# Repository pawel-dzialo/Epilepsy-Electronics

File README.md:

# Epilepsy detection electronics

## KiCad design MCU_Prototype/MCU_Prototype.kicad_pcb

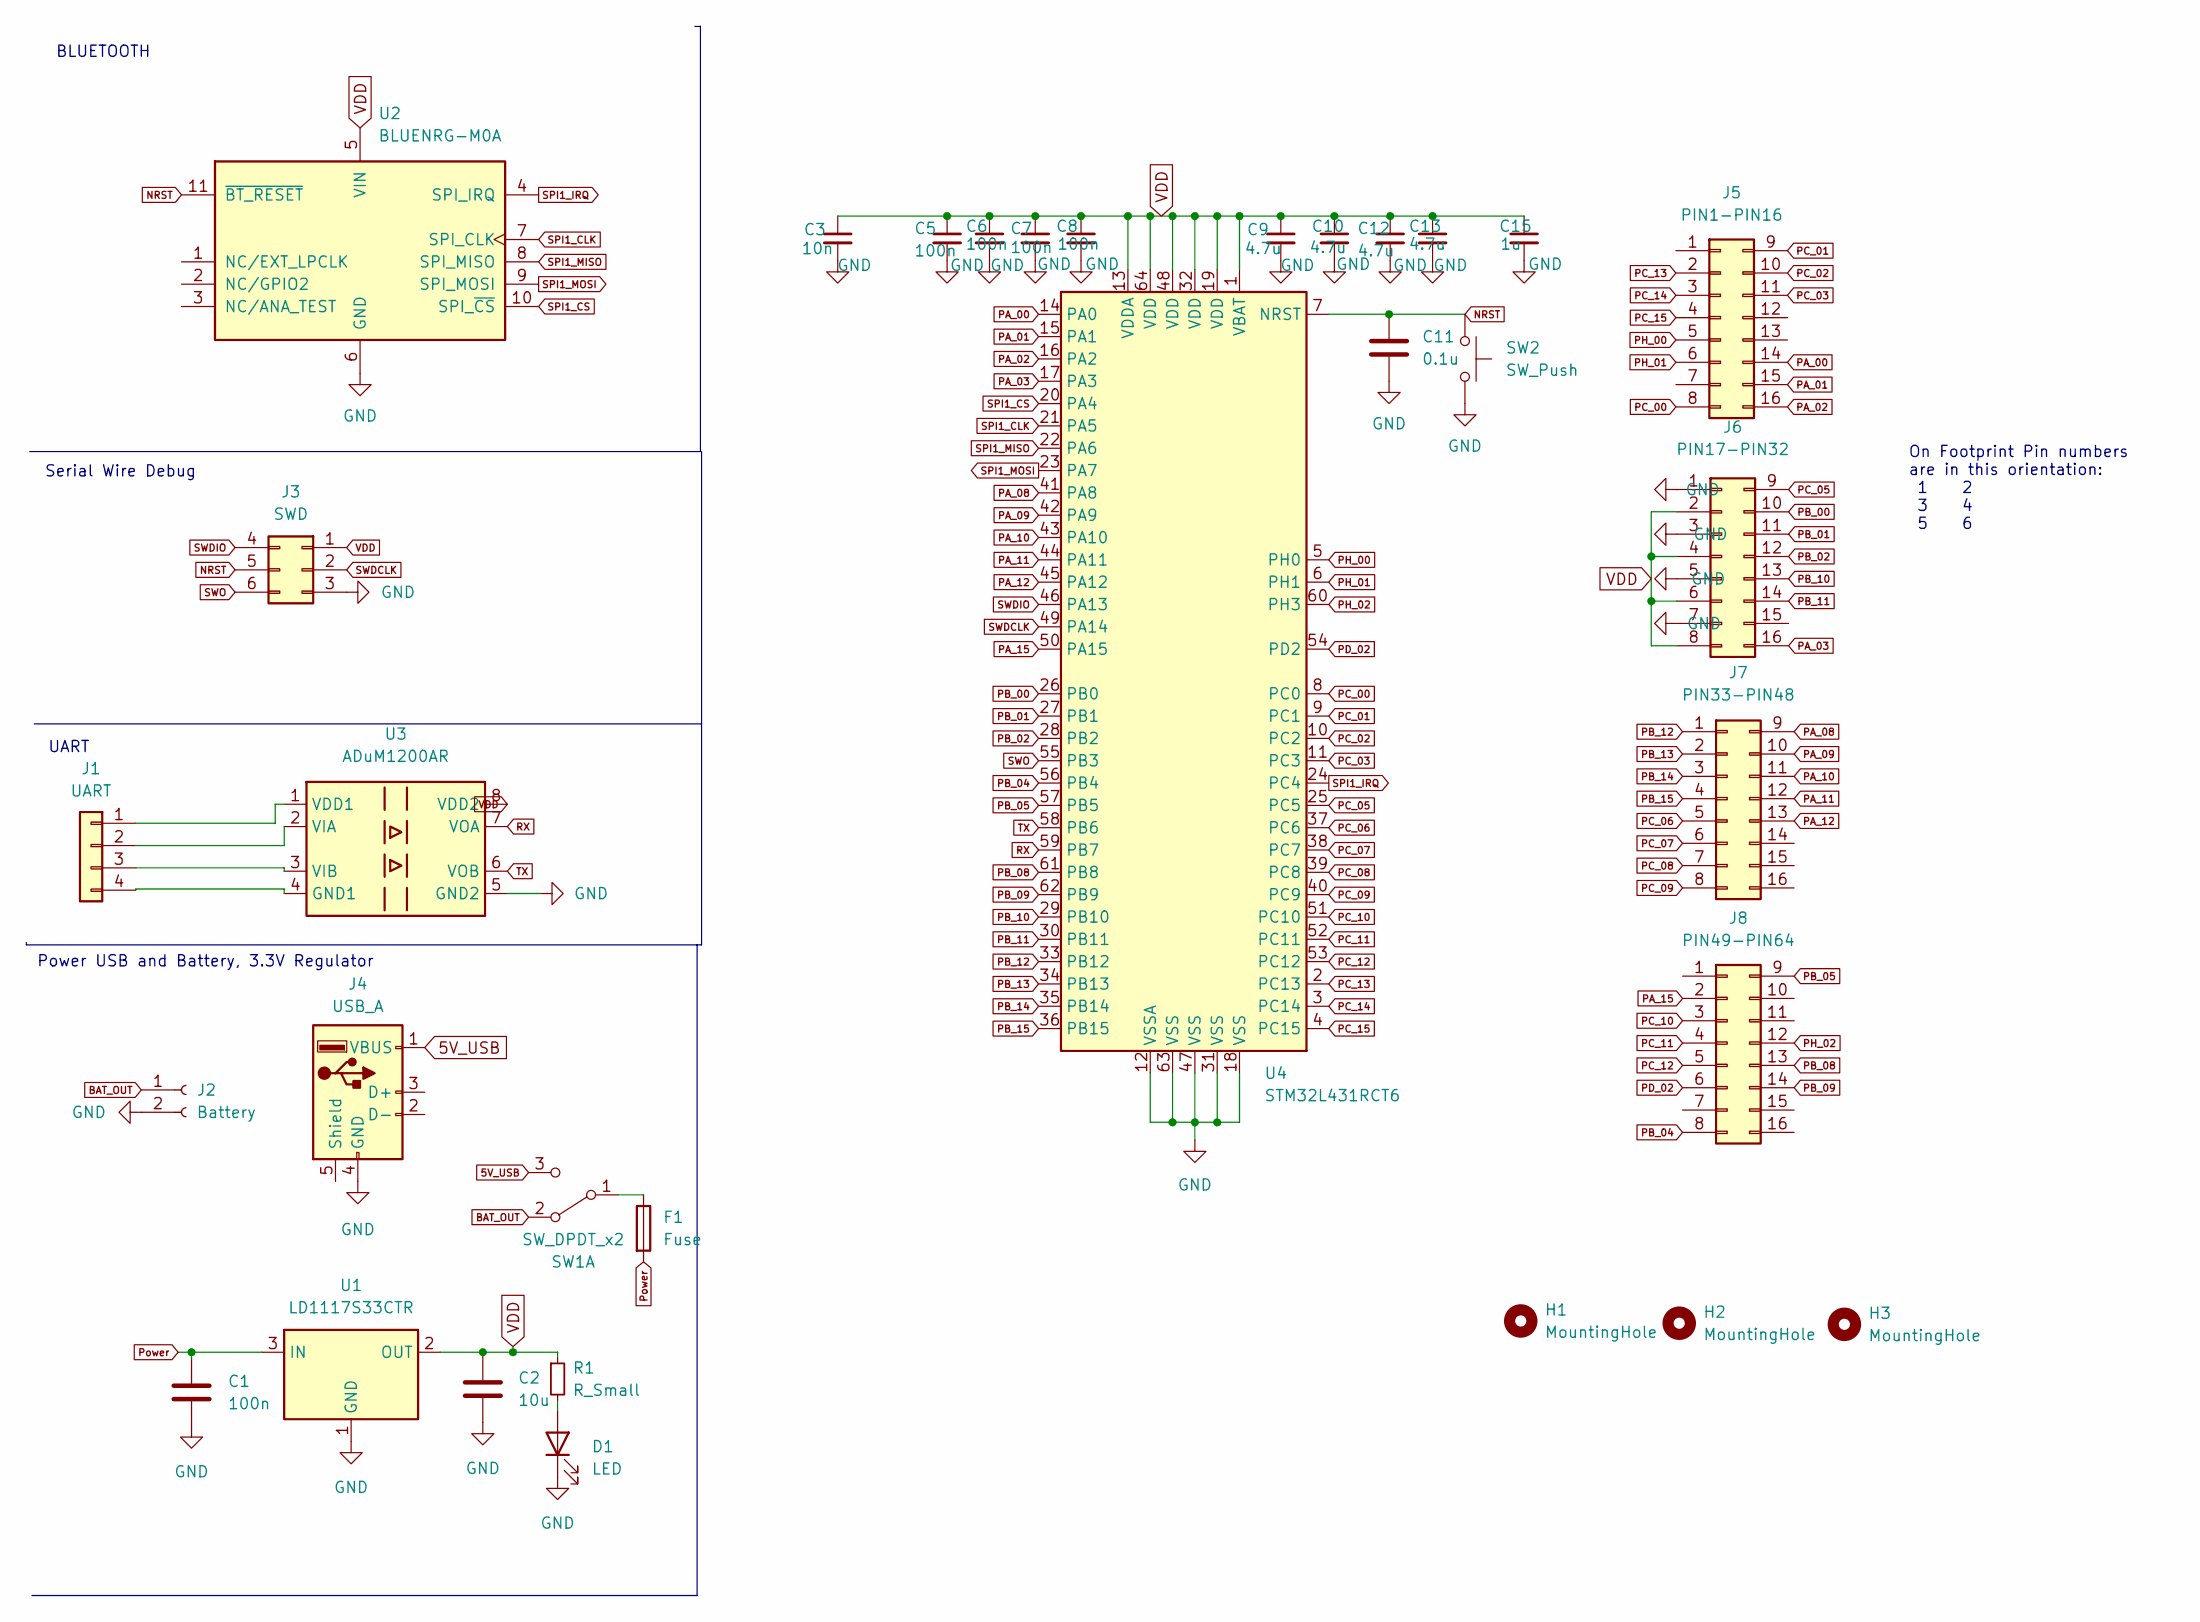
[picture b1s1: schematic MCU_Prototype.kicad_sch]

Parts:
C1, C5, C6, C7, C8: 100n; C_0805_2012Metric
C2: 10u; CP_Radial_D5.0mm_P2.00mm
C3: 10n; C_0805_2012Metric
C9, C10, C12, C13: 4.7u; CP_Radial_D5.0mm_P2.00mm
C11: 0.1u; C_0805_2012Metric
C15: 1u; CP_Radial_D5.0mm_P2.00mm
D1: LED
F1: Fuse; Fuse_Rad
H1, H2, H3: MountingHole; MountingHole_3.2mm_M3_DIN965_Pad
J1: UART; PinHeader_1x04_P2.54mm_Vertical
J2: Battery; JST_PH_S2B-PH-K_1x02_P2.00mm_Horizontal
J3: SWD; PinHeader_1x06_P2.54mm_Vertical
J4: USB_A; USBA
J5: PIN1-PIN16; PinHeader_2x08_P2.54mm_Vertical
J6: PIN17-PIN32; PinHeader_2x08_P2.54mm_Vertical
J7: PIN33-PIN48; PinHeader_2x08_P2.54mm_Vertical
J8: PIN49-PIN64; PinHeader_2x08_P2.54mm_Vertical
R1: R_Small; R_0805_2012Metric
SW1: SW_DPDT_x2; Switch
SW2: SW_Push; Button
U1: LD1117S33CTR; SOT223
U2: BLUENRG-M0A; ST_SPBTLE
U3: ADuM1200AR; SOIC127P600X175-8N
U4: STM32L431RCT6; LQFP-64_10x10mm_P0.5mm

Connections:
5V_USB: J4.1 (VBUS), SW1.3 (C)
BAT_OUT: J2.1, SW1.2 (A)
GND: C1.2, C2.2, C3.2, C5.2, C6.2, C7.2, C8.2, C9.2, C10.2, C11.2, C12.2, C13.2, C15.2, D1.1 (K), J2.2, J3.3, J4.4 (GND), J6.1, J6.3, J6.5, J6.7, SW2.2, U1.1 (GND), U1.5 (GND), U2.6 (GND), U3.5 (GND2), U4.12 (VSSA), U4.18 (VSS), U4.31 (VSS), U4.47 (VSS), U4.63 (VSS)
NRST: C11.1, J3.5, SW2.1, U2.11 (~BT_RESET), U4.7 (NRST)
unnamed: D1.2 (A), R1.2
unnamed: F1.1, SW1.1 (B)
unnamed: J1.1, U3.1 (VDD1)
unnamed: J1.2, U3.2 (VIA)
unnamed: J1.3, U3.3 (VIB)
unnamed: J1.4, U3.4 (GND1)
PA_00: J5.14, U4.14 (PA0)
PA_01: J5.15, U4.15 (PA1)
PA_02: J5.16, U4.16 (PA2)
PA_03: J6.16, U4.17 (PA3)
PA_08: J7.9, U4.41 (PA8)
PA_09: J7.10, U4.42 (PA9)
PA_10: J7.11, U4.43 (PA10)
PA_11: J7.12, U4.44 (PA11)
PA_12: J7.13, U4.45 (PA12)
PA_15: J8.2, U4.50 (PA15)
PB_00: J6.10, U4.26 (PB0)
PB_01: J6.11, U4.27 (PB1)
PB_02: J6.12, U4.28 (PB2)
PB_04: J8.8, U4.56 (PB4)
PB_05: J8.9, U4.57 (PB5)
PB_08: J8.13, U4.61 (PB8)
PB_09: J8.14, U4.62 (PB9)
PB_10: J6.13, U4.29 (PB10)
PB_11: J6.14, U4.30 (PB11)
PB_12: J7.1, U4.33 (PB12)
PB_13: J7.2, U4.34 (PB13)
PB_14: J7.3, U4.35 (PB14)
PB_15: J7.4, U4.36 (PB15)
PC_00: J5.8, U4.8 (PC0)
PC_01: J5.9, U4.9 (PC1)
PC_02: J5.10, U4.10 (PC2)
PC_03: J5.11, U4.11 (PC3)
PC_05: J6.9, U4.25 (PC5)
PC_06: J7.5, U4.37 (PC6)
PC_07: J7.6, U4.38 (PC7)
PC_08: J7.7, U4.39 (PC8)
PC_09: J7.8, U4.40 (PC9)
PC_10: J8.3, U4.51 (PC10)
PC_11: J8.4, U4.52 (PC11)
PC_12: J8.5, U4.53 (PC12)
PC_13: J5.2, U4.2 (PC13)
PC_14: J5.3, U4.3 (PC14)
PC_15: J5.4, U4.4 (PC15)
PD_02: J8.6, U4.54 (PD2)
PH_00: J5.5, U4.5 (PH0)
PH_01: J5.6, U4.6 (PH1)
PH_02: J8.12, U4.60 (PH3)
Power: C1.1, F1.2, U1.3 (IN)
RX: U3.7 (VOA), U4.59 (PB7)
SPI1_CLK: U2.7 (SPI_CLK), U4.21 (PA5)
SPI1_CS: U2.10 (SPI_~CS), U4.20 (PA4)
SPI1_IRQ: U2.4 (SPI_IRQ), U4.24 (PC4)
SPI1_MISO: U2.8 (SPI_MISO), U4.22 (PA6)
SPI1_MOSI: U2.9 (SPI_MOSI), U4.23 (PA7)
SWDCLK: J3.2, U4.49 (PA14)
SWDIO: J3.4, U4.46 (PA13)
SWO: J3.6, U4.55 (PB3)
TX: U3.6 (VOB), U4.58 (PB6)
VDD: C2.1, C3.1, C5.1, C6.1, C7.1, C8.1, C9.1, C10.1, C12.1, C13.1, C15.1, J3.1, J6.2, J6.4, J6.6, J6.8, R1.1, U1.2 (OUT), U2.5 (VIN), U3.8 (VDD2), U4.1 (VBAT), U4.13 (VDDA), U4.19 (VDD), U4.32 (VDD), U4.48 (VDD), U4.64 (VDD)

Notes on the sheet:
UART
BLUETOOTH
Serial Wire Debug
Power USB and Battery, 3.3V Regulator
On Footprint Pin numbers are in this orientation: 1 2 3 4 5 6

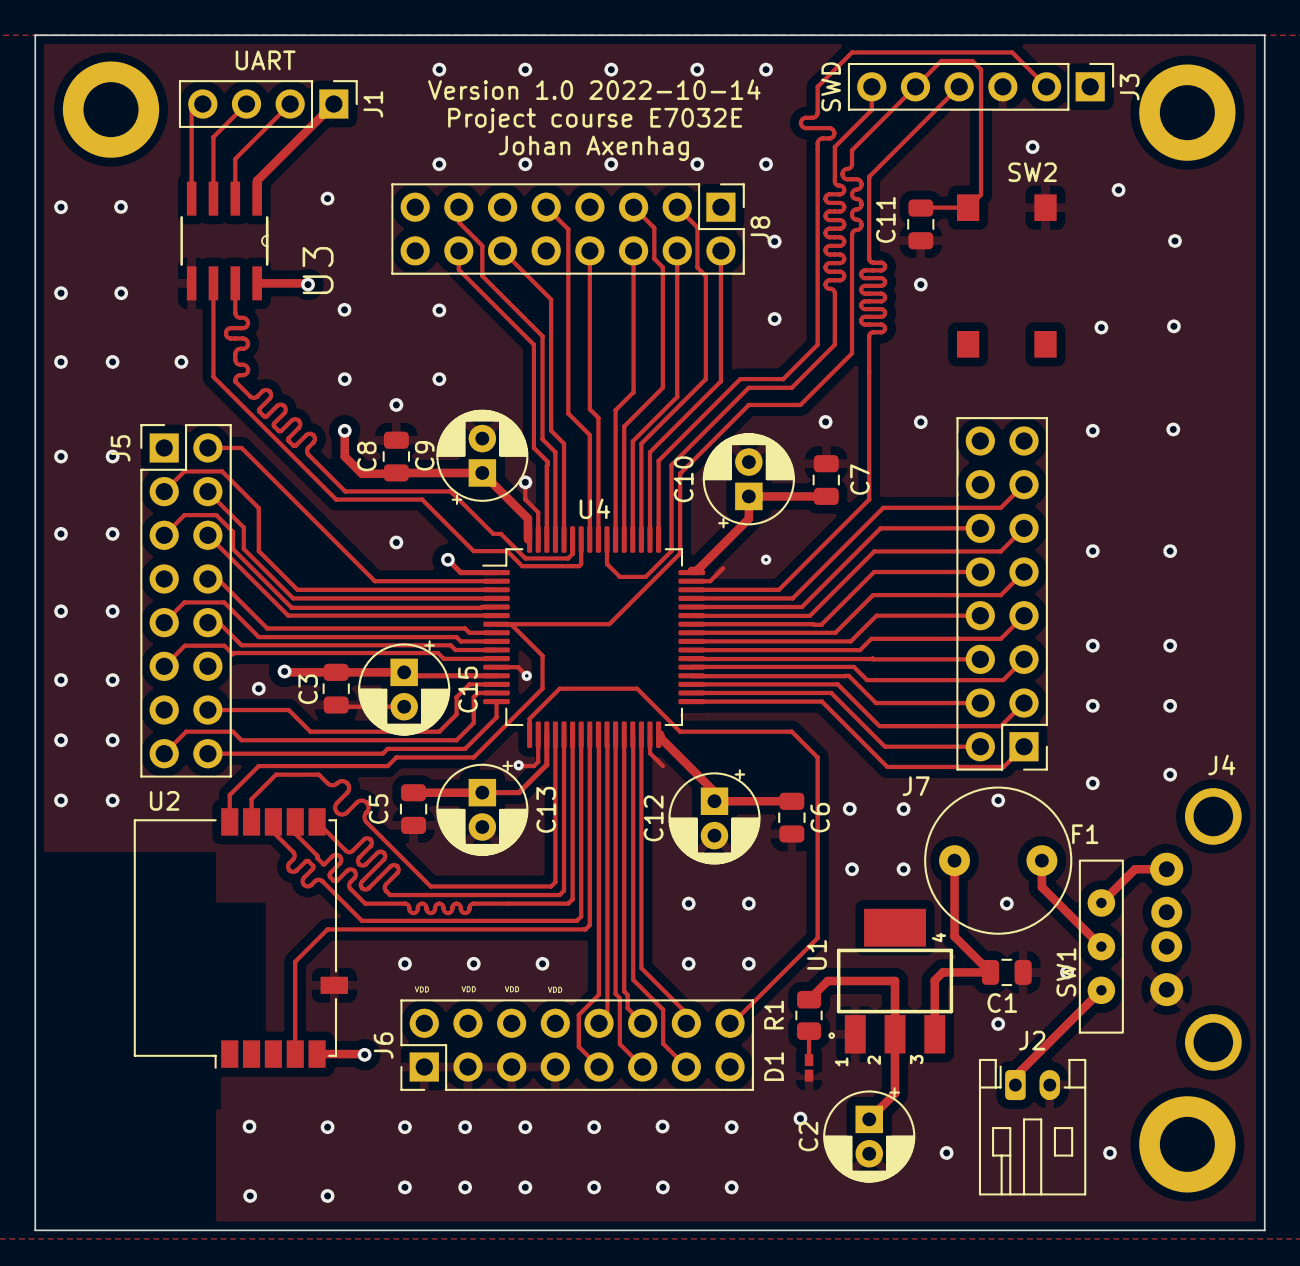
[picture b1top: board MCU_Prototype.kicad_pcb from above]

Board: 4 copper layers, 71.5 x 69.5 mm, 33 parts (0 on the bottom side), 64 nets.

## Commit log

2022-10-03 bad code dont look
2022-10-13 PCB MCU prototype
2022-10-13 Routed VDD and GND
2022-10-14 Cleaned up some errors
    +Made it more comapct
    +Added Ground vias
    +Change the order of the nets
2022-10-14 Added silkscreen
